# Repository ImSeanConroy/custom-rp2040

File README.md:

# Custom RP2040

Complete design files for an RP2040 microcontroller-based board, created using KiCad.

## Contributing

Contributions are welcome. Please open an issue or fork the repository, create a new branch (`feature/your-feature-name`) and submit a pull request for any enhancements or bug fixes.

## License

This project is licensed under the MIT License - see the [LICENSE](LICENSE) file for information.

## Support

If you are having problems, please let me know by [raising a new issue](https://github.com/ImSeanConroy/custom-rp2040/issues/new/choose).

## Acknowledgments

A special thanks to the creators of these invaluable resources that helped guide this project:

- [Custom RP2040 PCB Design in KiCAD](https://deepbluembedded.com/raspberry-pi-pico-rp2040-schematic-pcb-design-in-kicad/): Raspberry Pi Pico (RP2040) Schematic & PCB Design in KiCAD by Khaled Magdy
- [Hardware design for the RP2040](https://github.com/calliah333/RP2040-designguide/tree/main?tab=readme-ov-file#voltage-regulator): by calliah333

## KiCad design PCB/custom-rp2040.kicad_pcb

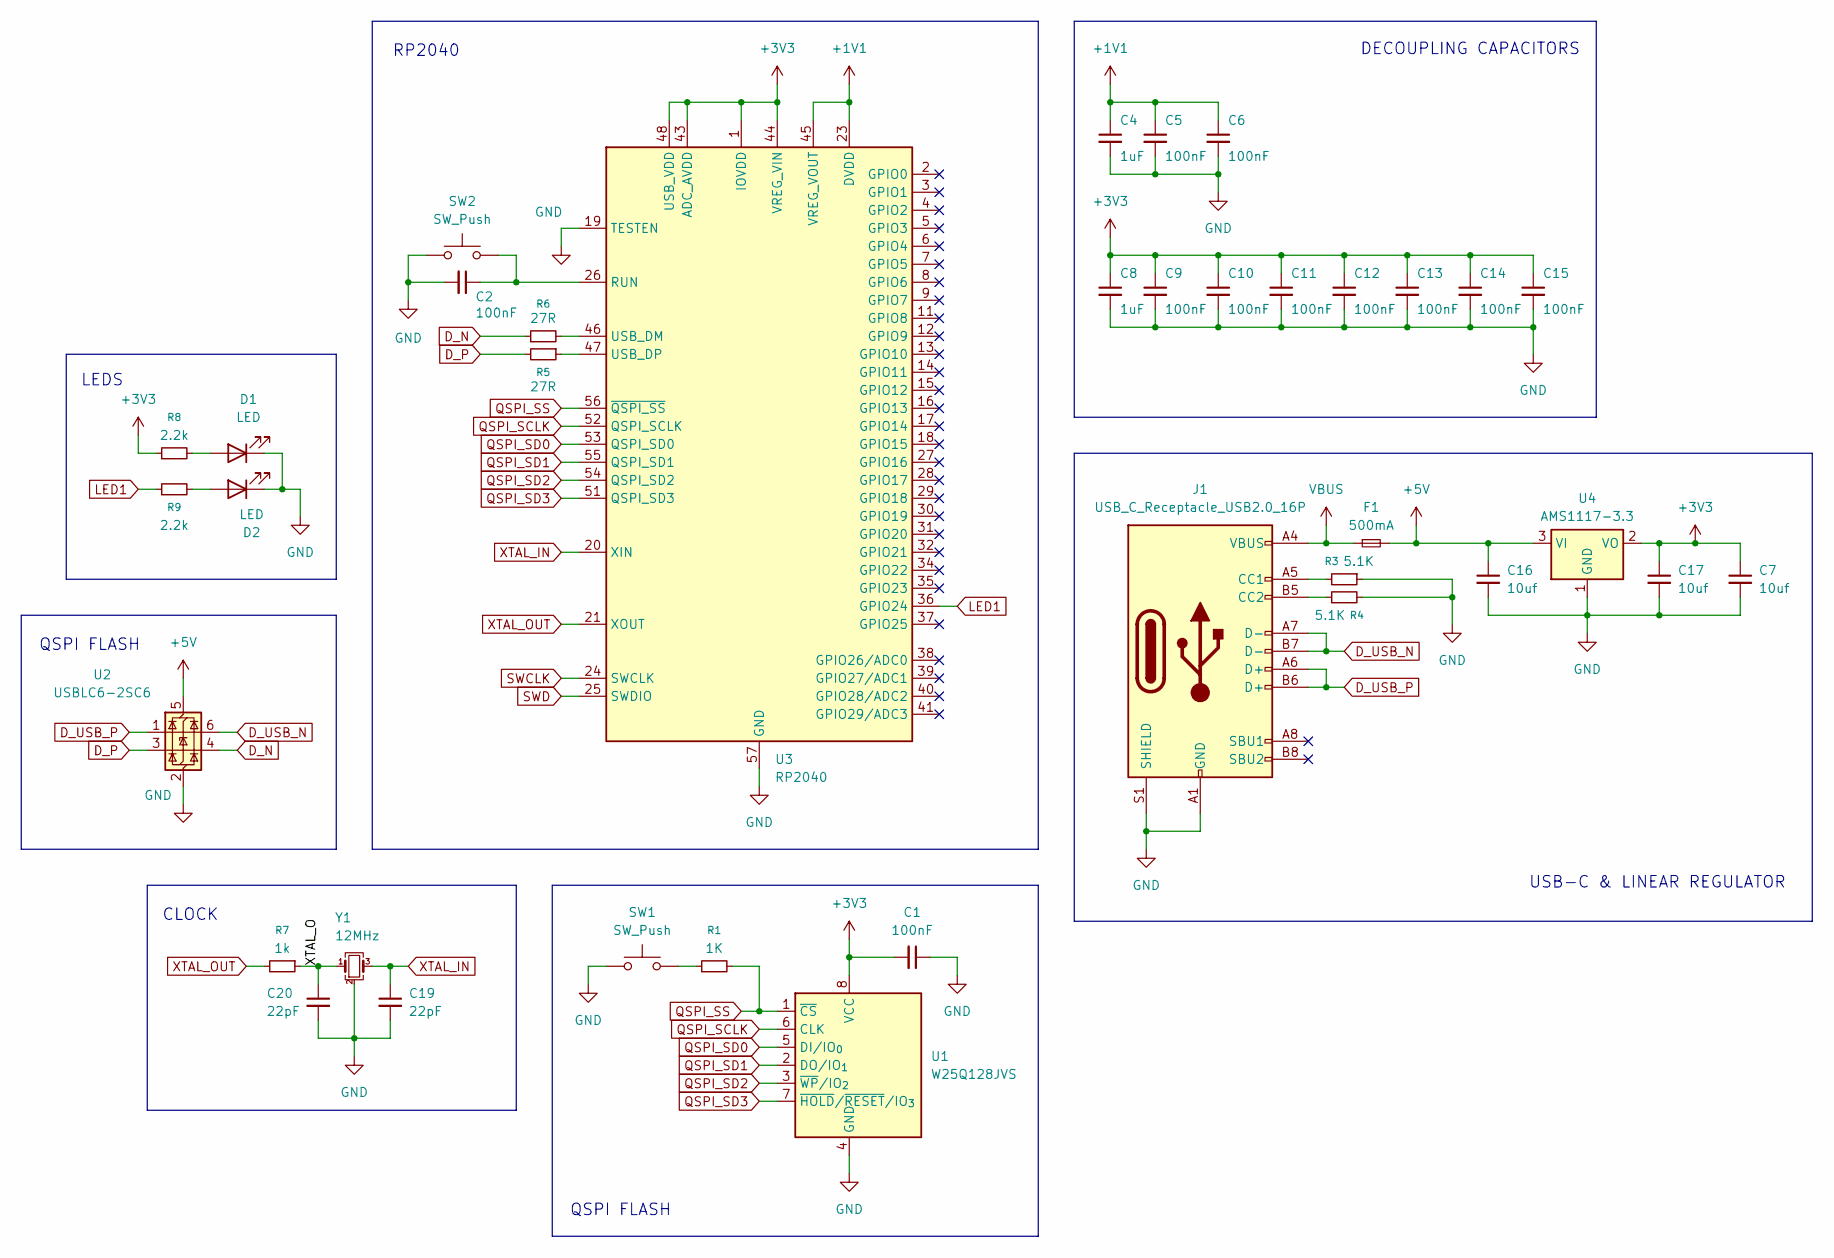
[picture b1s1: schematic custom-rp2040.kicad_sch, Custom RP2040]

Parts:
C1: 100nF; C_0402_1005Metric
C2, C5, C6, C9, C10, C11, C12, C13, C14, C15: 100nF; C_0402_1005Metric; LCSC C1525
C4, C8: 1uF; C_0402_1005Metric; LCSC C52923
C7, C16, C17: 10uf; C_0402_1005Metric
C19, C20: 22pF; C_0402_1005Metric
D1, D2: LED; LED_0402_1005Metric
F1: 500mA; Fuse_1206_3216Metric
J1: USB_C_Receptacle_USB2.0_16P; USB_C_Receptacle_HCTL_HC-TYPE-C-16P-01A
R1: 1K; R_0402_1005Metric
R3, R4: 5.1K; R_0402_1005Metric
R5, R6: 27R; R_0402_1005Metric
R7: 1k; R_0402_1005Metric
R8, R9: 2.2k; R_0402_1005Metric
SW1, SW2: SW_Push; SW_SPST_PTS810
U1: W25Q128JVS; SOIC-8_5.3x5.3mm_P1.27mm
U2: USBLC6-2SC6; SOT-23-6; LCSC C2827654
U3: RP2040; QFN-56-1EP_7x7mm_P0.4mm_EP3.2x3.2mm
U4: AMS1117-3.3; SOT-223-3_TabPin2
Y1: 12MHz; Crystal_SMD_3225-4Pin_3.2x2.5mm; LCSC C9002

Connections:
+1V1: C4.1, C5.1, C6.1, U3.23 (DVDD), U3.45 (VREG_VOUT), U3.50 (DVDD)
+3V3: C1.2, C7.1, C8.1, C9.1, C10.1, C11.1, C12.1, C13.1, C14.1, C15.1, C17.1, R8.1, U1.8 (VCC), U3.1 (IOVDD), U3.10 (IOVDD), U3.22 (IOVDD), U3.33 (IOVDD), U3.42 (IOVDD), U3.43 (ADC_AVDD), U3.44 (VREG_VIN), U3.48 (USB_VDD), U3.49 (IOVDD), U4.2 (VO)
+5V: C16.1, F1.2, U2.5 (VBUS), U4.3 (VI)
/XTAL_O: C20.1, R7.1, Y1.1
D_N: R6.1, U2.4 (I/O2)
D_P: R5.2, U2.3 (I/O2)
D_USB_N: J1.A7 (D-), J1.B7 (D-), U2.6 (I/O1)
D_USB_P: J1.A6 (D+), J1.B6 (D+), U2.1 (I/O1)
GND: C1.1, C2.2, C4.2, C5.2, C6.2, C7.2, C8.2, C9.2, C10.2, C11.2, C12.2, C13.2, C14.2, C15.2, C16.2, C17.2, C19.2, C20.2, D1.1 (K), D2.1 (K), J1.A1 (GND), J1.A12 (GND), J1.B1 (GND), J1.B12 (GND), J1.S1 (SHIELD), R3.1, R4.2, SW1.1, SW2.1, U1.4 (GND), U2.2 (GND), U3.19 (TESTEN), U3.57 (GND), U4.1 (GND), Y1.2 (G), Y1.4 (G)
LED1: R9.1, U3.36 (GPIO24)
unnamed: D1.2 (A), R8.2
unnamed: D2.2 (A), R9.2
unnamed: J1.A5 (CC1), R3.2
unnamed: J1.B5 (CC2), R4.1
unnamed: R1.1, SW1.2
unnamed: C2.1, SW2.2, U3.26 (RUN)
unnamed: R6.2, U3.46 (USB_DM)
unnamed: R5.1, U3.47 (USB_DP)
QSPI_SCLK: U1.6 (CLK), U3.52 (QSPI_SCLK)
QSPI_SD0: U1.5 (DI/IO_{0}), U3.53 (QSPI_SD0)
QSPI_SD1: U1.2 (DO/IO_{1}), U3.55 (QSPI_SD1)
QSPI_SD2: U1.3 (~WP/IO_{2}), U3.54 (QSPI_SD2)
QSPI_SD3: U1.7 (~HOLD/~RESET/IO_{3}), U3.51 (QSPI_SD3)
QSPI_SS: R1.2, U1.1 (~CS), U3.56 (~QSPI_SS)
SWCLK: U3.24 (SWCLK)
SWD: U3.25 (SWDIO)
VBUS: F1.1, J1.A4 (VBUS), J1.A9 (VBUS), J1.B4 (VBUS), J1.B9 (VBUS)
XTAL_IN: C19.1, U3.20 (XIN), Y1.3
XTAL_OUT: R7.2, U3.21 (XOUT)

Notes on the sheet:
RP2040
DECOUPLING CAPACITORS
LEDS
USB-C & LINEAR REGULATOR
QSPI FLASH
CLOCK

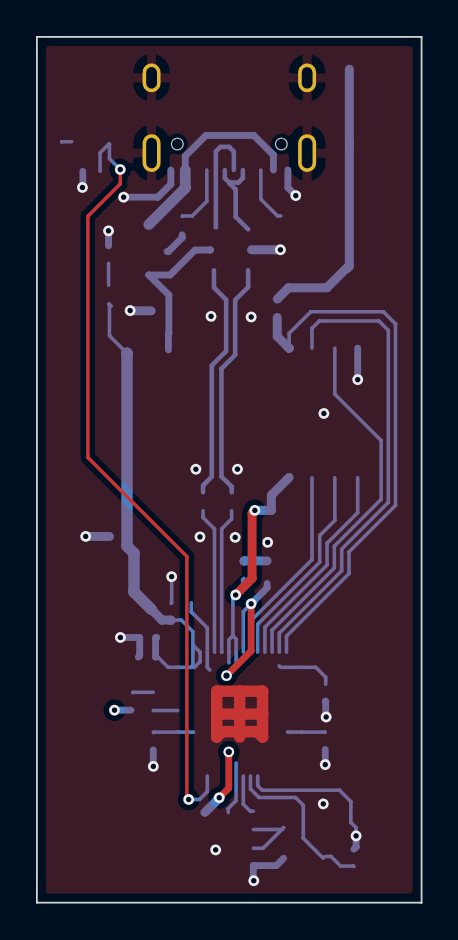
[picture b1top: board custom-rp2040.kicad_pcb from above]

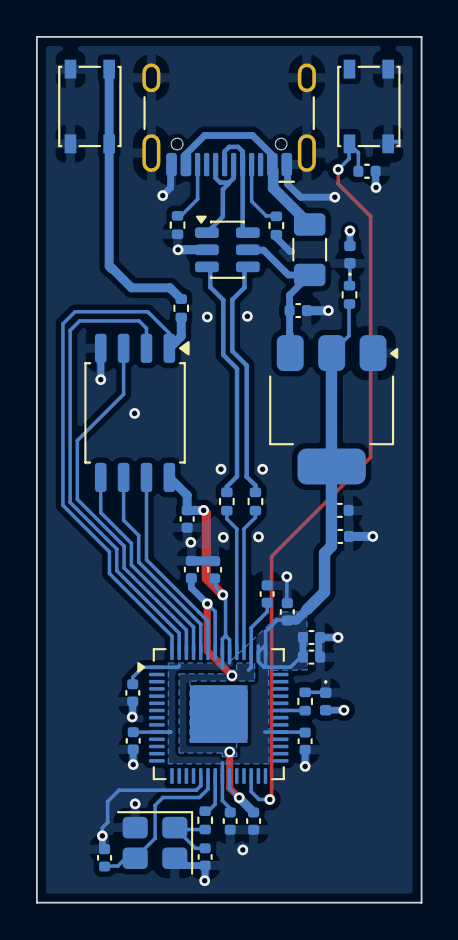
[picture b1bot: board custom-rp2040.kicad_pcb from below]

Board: 2 copper layers, 21.4 x 48.1 mm, 37 parts (37 on the bottom side), 27 nets.

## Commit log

2026-03-29 Layout schematic
2026-03-29 Layout board
2026-03-30 Add reset and boot buttons
